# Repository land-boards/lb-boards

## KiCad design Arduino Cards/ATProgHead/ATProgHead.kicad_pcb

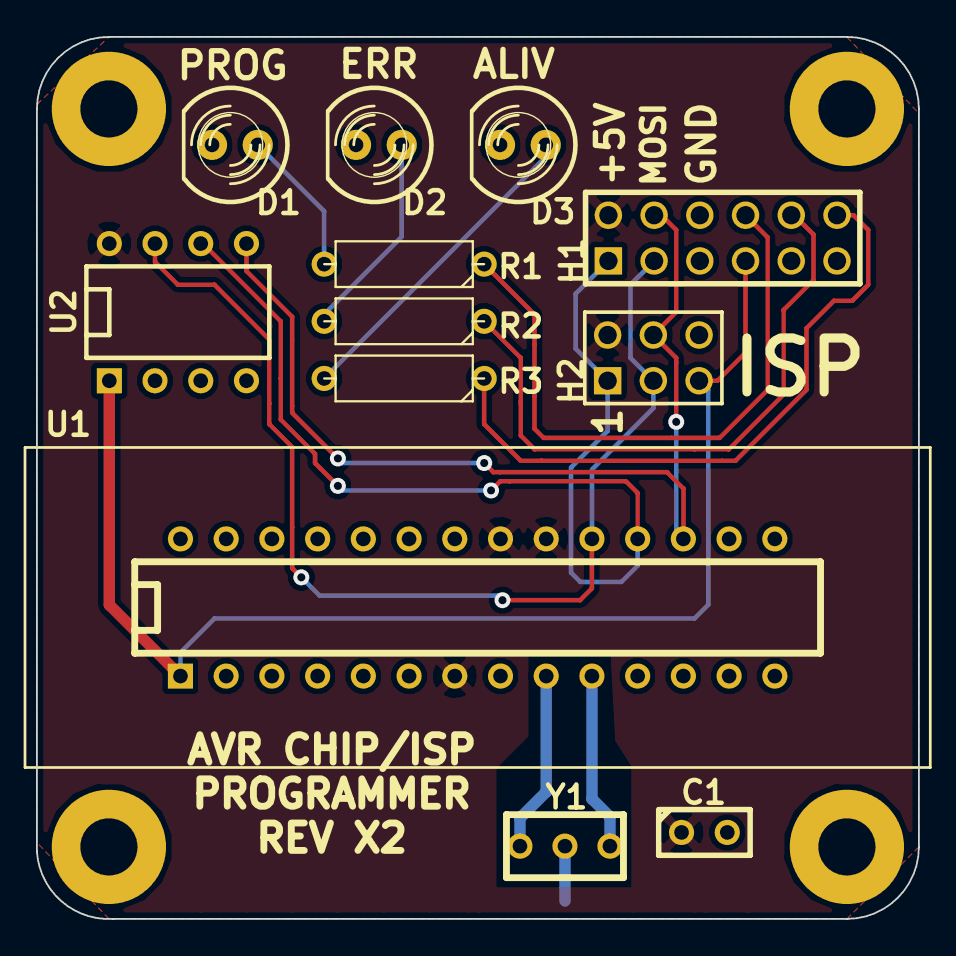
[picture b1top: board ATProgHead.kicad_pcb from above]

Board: 2 copper layers, 49.0 x 49.0 mm, 16 parts (0 on the bottom side), 14 nets.

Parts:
C1: 0.1uF; C1
D1, D2, D3: LED; LED-5MM
H1: CONN_6X2; pin_array_6x2
H2: CONN_3X2; pin_array_3x2
MTG1, MTG2, MTG3, MTG4: CONN_1; MTG-4-40
R1, R2, R3: 330; R3-5
U1: ATMEGA328-PU; TEXTOOL-28N
U2: ATTINY85; DIP-8__300
Y1: 16MHz; RESON_3PIN

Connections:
+5V: C1.1, H1.2, H2.2, U1.7, U1.20, U1.21, U2.8
/ER: D2.1, R2.2
/ERR-D8: H1.10, R2.1
/HB: D3.1, R3.2
/HTBT-D9: H1.12, R3.1
/MISO-D12: H1.1, H2.1, U1.18, U2.6
/MOSI-D11: H1.4, H2.4, U1.17, U2.5
/PG: D1.1, R1.2
/PROG-D7: H1.8, R1.1
/RST-D10: H1.7, H2.5, U1.1, U2.1
/SCK-D13: H1.3, H2.3, U1.19, U2.7
GND: C1.2, D1.2, D2.2, D3.2, H1.6, H2.6, U1.8, U1.22, U2.4, Y1.2
unnamed: U1.9, Y1.1
unnamed: U1.10, Y1.3

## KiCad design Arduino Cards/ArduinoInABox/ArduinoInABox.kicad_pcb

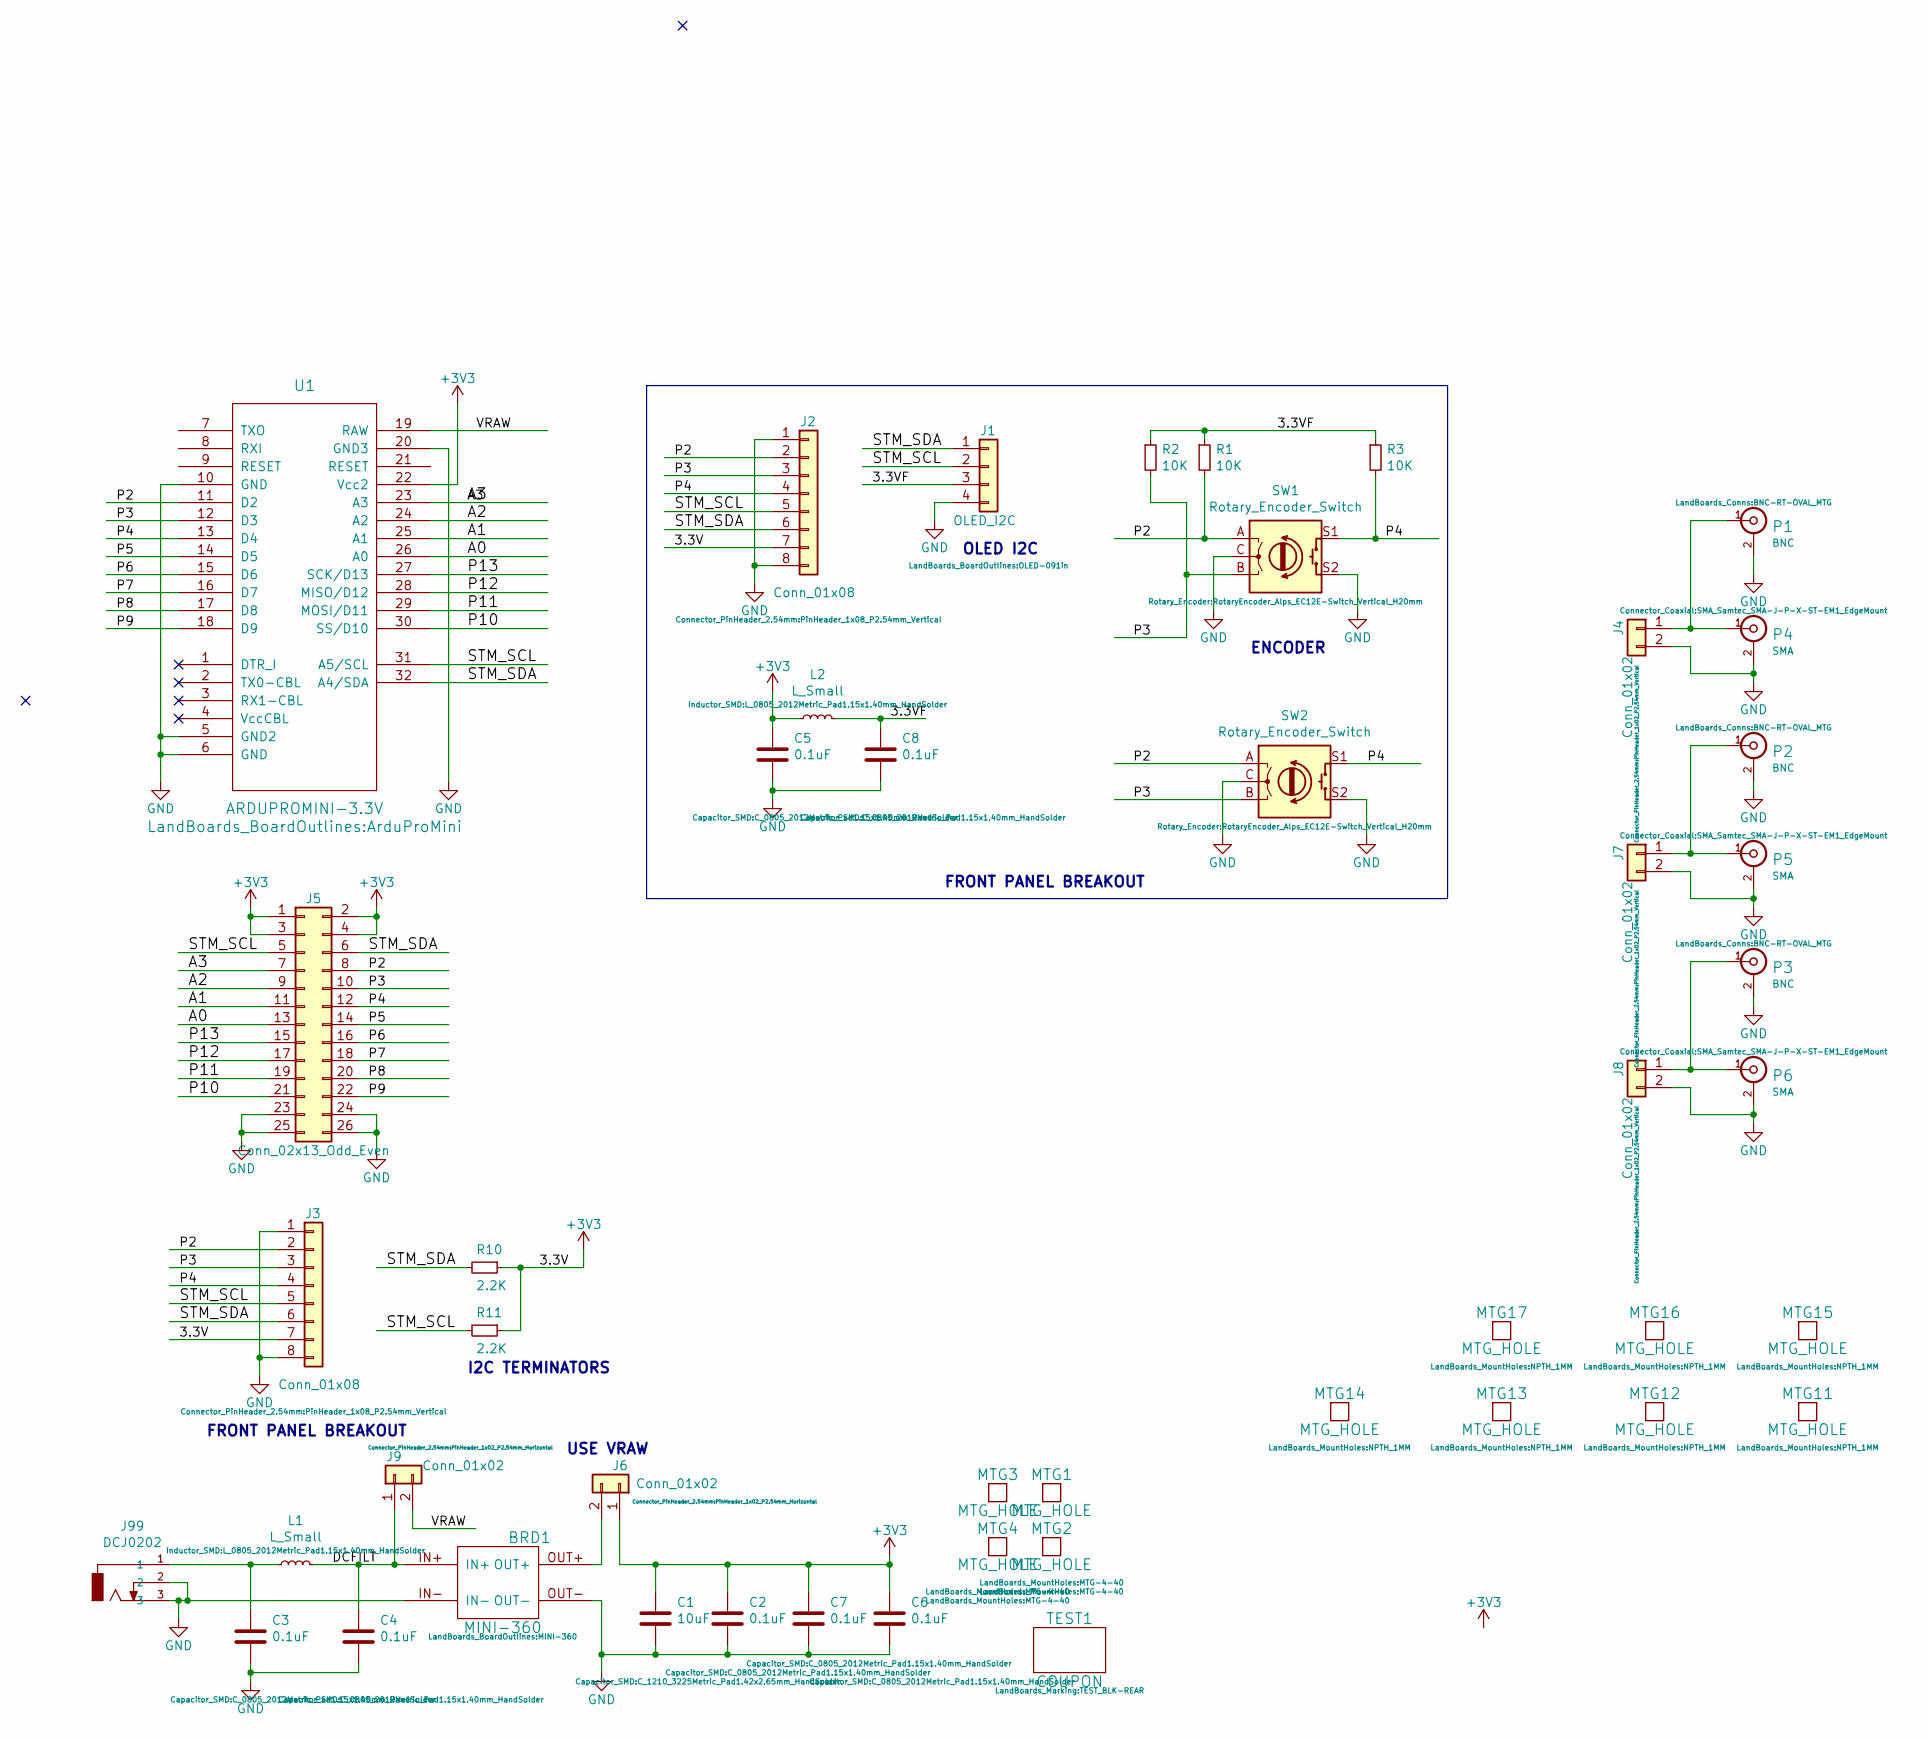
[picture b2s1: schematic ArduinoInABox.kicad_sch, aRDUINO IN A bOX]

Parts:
BRD1: MINI-360
C1: 10uF; C_1210_3225Metric_Pad1.42x2.65mm_HandSolder
C2, C3, C4, C5, C6, C7, C8: 0.1uF; C_0805_2012Metric_Pad1.15x1.40mm_HandSolder
J1: OLED_I2C; OLED-091in
J2, J3: Conn_01x08; PinHeader_1x08_P2.54mm_Vertical
J4, J7, J8: Conn_01x02; PinHeader_1x02_P2.54mm_Vertical
J5: Conn_02x13_Odd_Even; PinHeader_2x13_P2.54mm_Vertical
J6, J9: Conn_01x02; PinHeader_1x02_P2.54mm_Horizontal
J99: DCJ0202; DCJ-NEW-Slotted
L1, L2: L_Small; L_0805_2012Metric_Pad1.15x1.40mm_HandSolder
MTG1, MTG2, MTG3, MTG4: MTG_HOLE; MTG-4-40
MTG11, MTG12, MTG13, MTG14, MTG15, MTG16, MTG17: MTG_HOLE; NPTH_1MM
P1, P2, P3: BNC; BNC-RT-OVAL_MTG
P4, P5, P6: SMA; SMA_Samtec_SMA-J-P-X-ST-EM1_EdgeMount
R1, R2, R3: 10K; R_0805_2012Metric_Pad1.15x1.40mm_HandSolder
R10, R11: 2.2K; R_0805_2012Metric_Pad1.15x1.40mm_HandSolder
SW1, SW2: Rotary_Encoder_Switch; RotaryEncoder_Alps_EC12E-Switch_Vertical_H20mm
TEST1: COUPON; TEST_BLK-REAR
U1: ARDUPROMINI-3.3V; ArduProMini

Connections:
+3V3: C1.1, C2.1, C5.1, C6.1, C7.1, J2.7, J3.7, J5.1, J5.2, J5.3, J5.4, J6.1, L2.1, R10.1, R11.1, U1.22 (Vcc2)
/3.3VF: C8.1, J1.3, L2.2, R1.1, R2.1, R3.1
/A0: J5.13, U1.26 (A0)
/A1: J5.11, U1.25 (A1)
/A2: J5.9, U1.24 (A2)
/A3: J5.7, U1.23 (A3)
/DCFILT: BRD1.IN+, C4.1, J9.1, L1.2
/P2: J2.2, J3.2, J5.8, R1.2, SW1.A, SW2.A, U1.11 (D2)
/P3: J2.3, J3.3, J5.10, R2.2, SW1.B, SW2.B, U1.12 (D3)
/P4: J2.4, J3.4, J5.12, R3.2, SW1.S1, SW2.S1, U1.13 (D4)
/P5: J5.14, U1.14 (D5)
/P6: J5.16, U1.15 (D6)
/P7: J5.18, U1.16 (D7)
/P8: J5.20, U1.17 (D8)
/P9: J5.22, U1.18 (D9)
/P10: J5.21, U1.30 (SS/D10)
/P11: J5.19, U1.29 (MOSI/D11)
/P12: J5.17, U1.28 (MISO/D12)
/P13: J5.15, U1.27 (SCK/D13)
/STM_SCL: J1.2, J2.5, J3.5, J5.5, R11.2, U1.31 (A5/SCL)
/STM_SDA: J1.1, J2.6, J3.6, J5.6, R10.2, U1.32 (A4/SDA)
/VRAW: J9.2, U1.19 (RAW)
GND: BRD1.IN-, BRD1.OUT-, C1.2, C2.2, C3.2, C4.2, C5.2, C6.2, C7.2, C8.2, J1.4, J2.1, J2.8, J3.1, J3.8, J4.2, J5.23, J5.24, J5.25, J5.26, J7.2, J8.2, J99.2, J99.3, P1.2 (Ext), P2.2 (Ext), P3.2 (Ext), P4.2 (Ext), P5.2 (Ext), P6.2 (Ext), SW1.C, SW1.S2, SW2.C, SW2.S2, U1.5 (GND2), U1.6 (GND), U1.10 (GND), U1.20 (GND3)
unnamed: BRD1.OUT+, J6.2
unnamed: C3.1, J99.1, L1.1
unnamed: J4.1, P1.1 (In), P4.1 (In)
unnamed: J7.1, P2.1 (In), P5.1 (In)
unnamed: J8.1, P3.1 (In), P6.1 (In)

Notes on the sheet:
OLED I2C
FRONT PANEL BREAKOUT
USE VRAW
ENCODER
I2C TERMINATORS

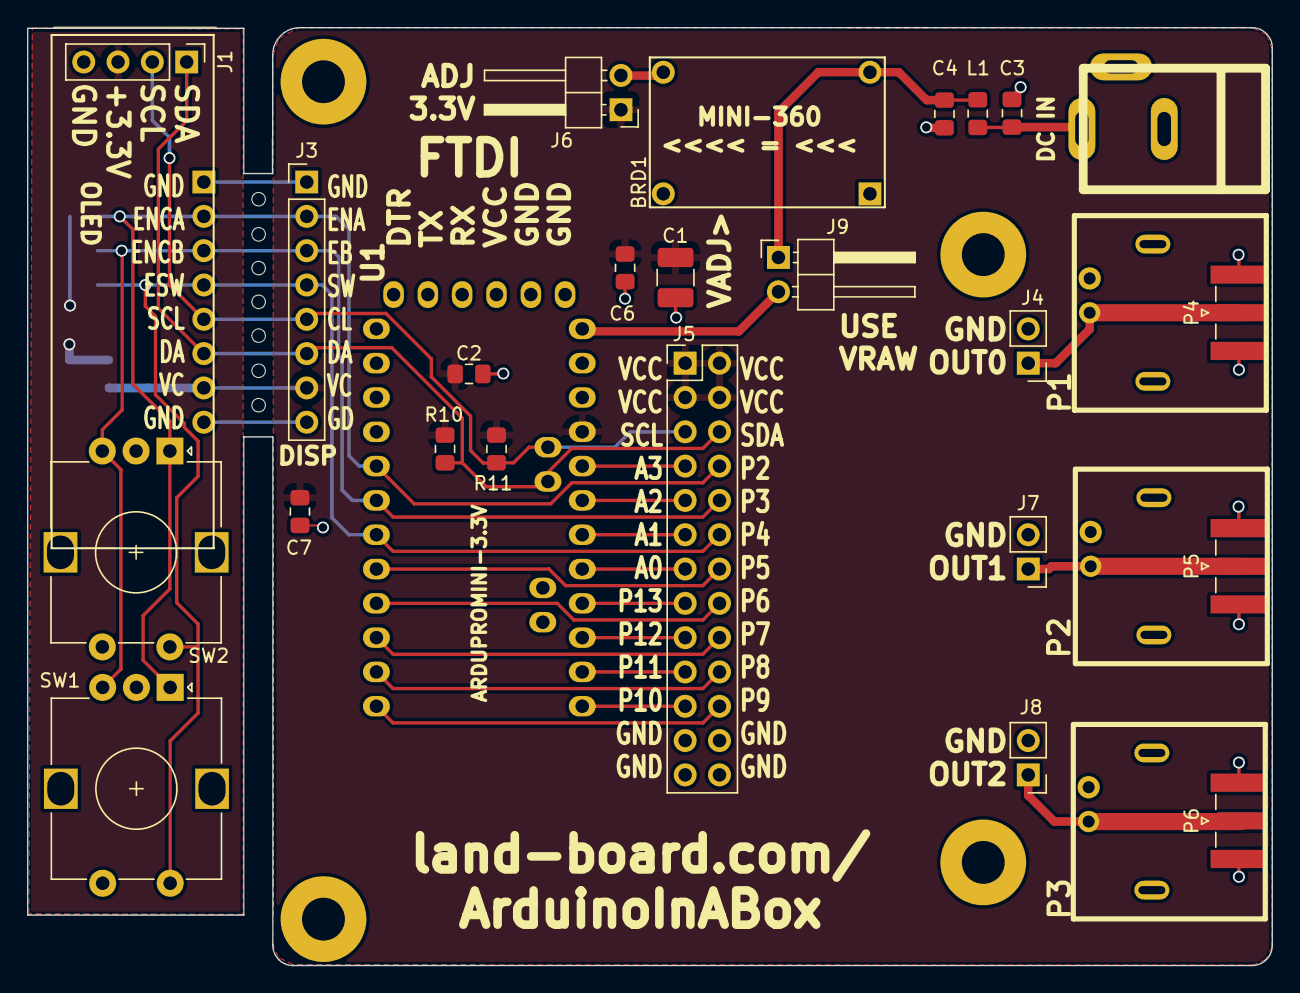
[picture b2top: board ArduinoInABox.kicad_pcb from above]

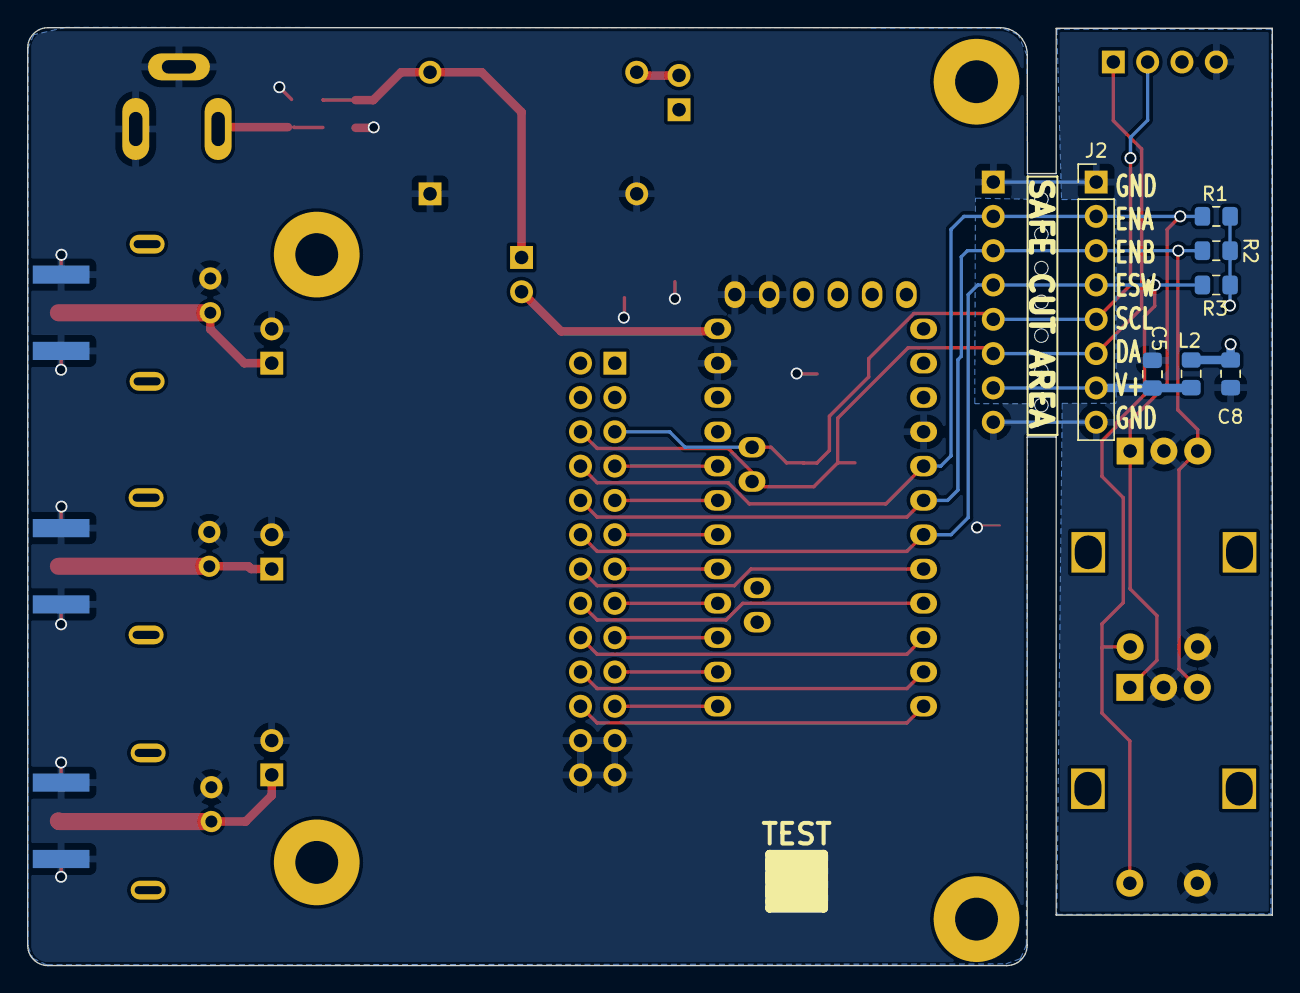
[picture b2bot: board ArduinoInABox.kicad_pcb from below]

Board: 2 copper layers, 92.2 x 69.4 mm, 47 parts (7 on the bottom side), 28 nets.

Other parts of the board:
TEST: COUPON; TEST_BLK-REAR

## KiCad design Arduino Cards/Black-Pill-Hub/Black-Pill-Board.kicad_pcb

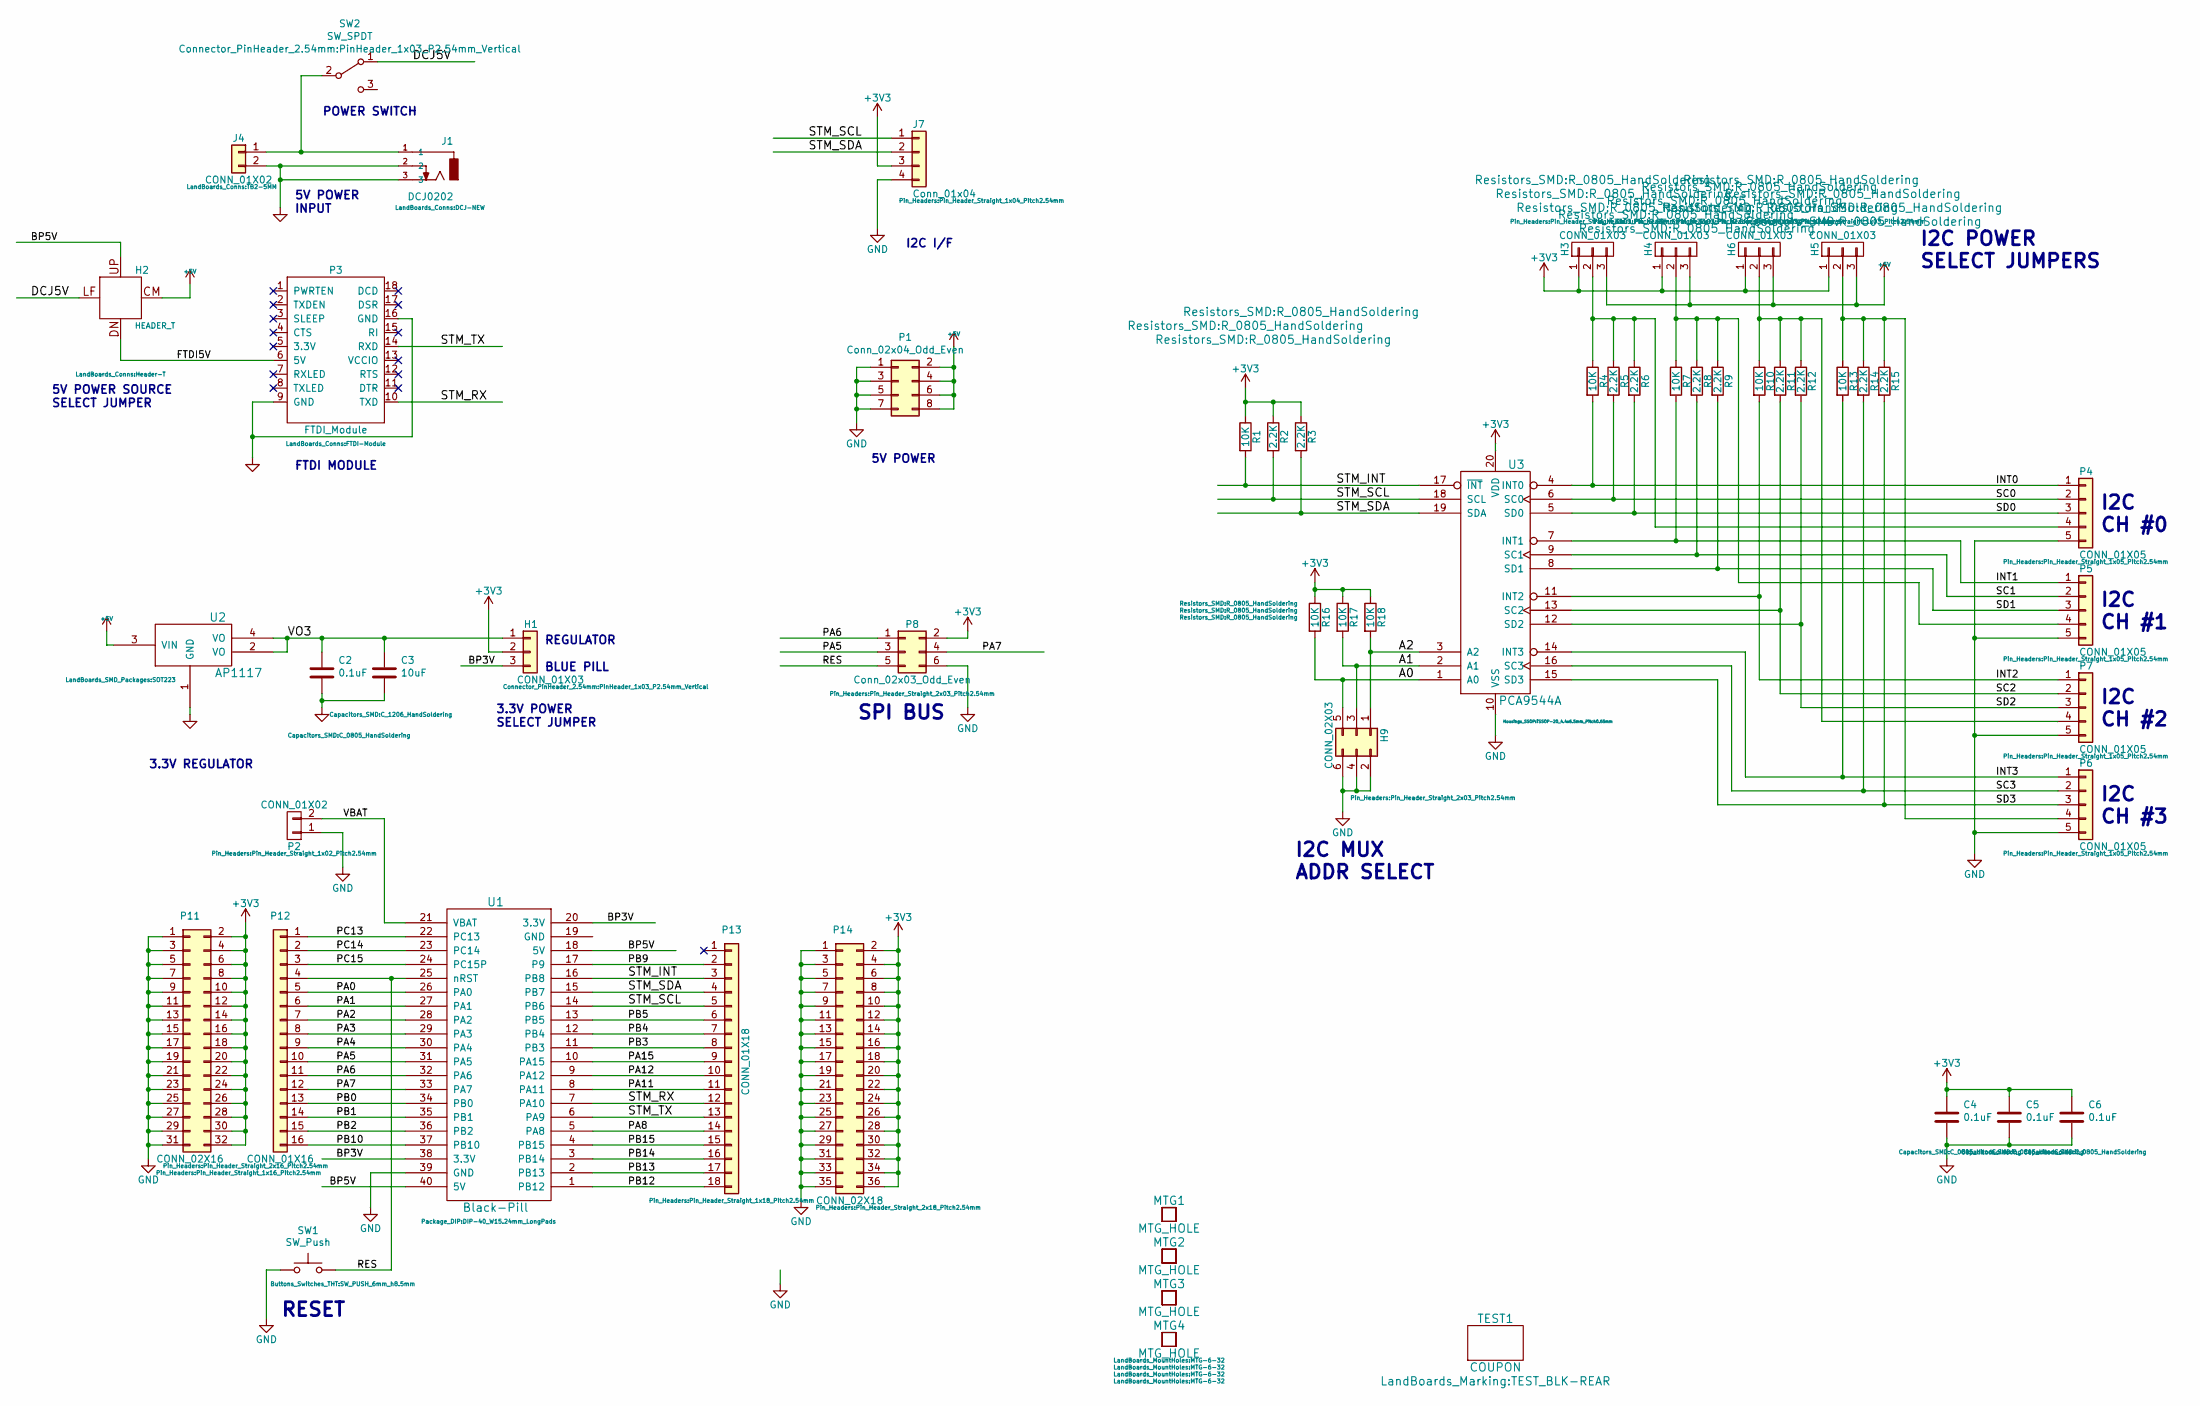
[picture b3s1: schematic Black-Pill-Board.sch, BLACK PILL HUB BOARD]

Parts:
C2, C4, C5, C6: 0.1uF; C_0805_HandSoldering
C3: 10uF; C_1206_HandSoldering
H1: CONN_01X03; PinHeader_1x03_P2.54mm_Vertical
H2: HEADER_T; Header-T
H3, H4, H5, H6: CONN_01X03; Pin_Header_Straight_1x03_Pitch2.54mm
H9: CONN_02X03; Pin_Header_Straight_2x03_Pitch2.54mm
J1: DCJ0202; DCJ-NEW
J4: CONN_01X02; TB2-5MM
J7: Conn_01x04; Pin_Header_Straight_1x04_Pitch2.54mm
MTG1, MTG2, MTG3, MTG4: MTG_HOLE; MTG-6-32
P1: Conn_02x04_Odd_Even; PinHeader_2x04_P2.54mm_Vertical
P2: CONN_01X02; Pin_Header_Straight_1x02_Pitch2.54mm
P3: FTDI_Module; FTDI-Module
P4, P5, P6, P7: CONN_01X05; Pin_Header_Straight_1x05_Pitch2.54mm
P8: Conn_02x03_Odd_Even; Pin_Header_Straight_2x03_Pitch2.54mm
P11: CONN_02X16; Pin_Header_Straight_2x16_Pitch2.54mm
P12: CONN_01X16; Pin_Header_Straight_1x16_Pitch2.54mm
P13: CONN_01X18; Pin_Header_Straight_1x18_Pitch2.54mm
P14: CONN_02X18; Pin_Header_Straight_2x18_Pitch2.54mm
R1, R4, R7, R10, R13, R16, R17, R18: 10K; R_0805_HandSoldering
R2, R3, R5, R6, R8, R9, R11, R12, R14, R15: 2.2K; R_0805_HandSoldering
SW1: SW_Push; SW_PUSH_6mm_h8.5mm
SW2: SW_SPDT; PinHeader_1x03_P2.54mm_Vertical
TEST1: COUPON; TEST_BLK-REAR
U1: Black-Pill; DIP-40_W15.24mm_LongPads
U2: AP1117; SOT223
U3: PCA9544A; TSSOP-20_4.4x6.5mm_Pitch0.65mm

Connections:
+3V3: C4.1, C5.1, C6.1, H1.2, H3.1, H4.1, H5.1, H6.1, J7.3, P8.2, P11.2, P11.4, P11.6, P11.8, P11.10, P11.12, P11.14, P11.16, P11.18, P11.20, P11.22, P11.24, P11.26, P11.28, P11.30, P11.32, P14.2, P14.4, P14.6, P14.8, P14.10, P14.12, P14.14, P14.16, P14.18, P14.20, P14.22, P14.24, P14.26, P14.28, P14.30, P14.32, P14.34, P14.36, R1.1, R2.1, R3.1, R16.1, R17.1, R18.1, U3.20 (VDD)
+5V: H2.CM (COM), H3.3, H4.3, H5.3, H6.3, P1.2, P1.4, P1.6, P1.8, U2.3 (VIN)
/A0: H9.5, R16.2, U3.1 (A0)
/A1: H9.3, R17.2, U3.2 (A1)
/A2: H9.1, R18.2, U3.3 (A2)
/BP3V: H1.3, U1.20 (3.3V), U1.38 (3.3V)
/BP5V: H2.UP, U1.18 (5V), U1.40 (5V)
/DCJ5V: H2.LF (LEFT), SW2.1 (A)
/FTDI5V: H2.DN (DOWN), P3.6 (5V)
/INT0: P4.1, R4.2, U3.4 (INT0)
/INT1: P5.1, R7.2, U3.7 (INT1)
/INT2: P7.1, R10.2, U3.11 (INT2)
/INT3: P6.1, R13.2, U3.14 (INT3)
/PA0: P12.5, U1.26 (PA0)
/PA1: P12.6, U1.27 (PA1)
/PA2: P12.7, U1.28 (PA2)
/PA3: P12.8, U1.29 (PA3)
/PA4: P12.9, U1.30 (PA4)
/PA5: P8.3, P12.10, U1.31 (PA5)
/PA6: P8.1, P12.11, U1.32 (PA6)
/PA7: P8.4, P12.12, U1.33 (PA7)
/PA8: P13.14, U1.5 (PA8)
/PA11: P13.11, U1.8 (PA11)
/PA12: P13.10, U1.9 (PA12)
/PA15: P13.9, U1.10 (PA15)
/PB0: P12.13, U1.34 (PB0)
/PB1: P12.14, U1.35 (PB1)
/PB2: P12.15, U1.36 (PB2)
/PB3: P13.8, U1.11 (PB3)
/PB4: P13.7, U1.12 (PB4)
/PB5: P13.6, U1.13 (PB5)
/PB9: P13.2, U1.17 (P9)
/PB10: P12.16, U1.37 (PB10)
/PB12: P13.18, U1.1 (PB12)
/PB13: P13.17, U1.2 (PB13)
/PB14: P13.16, U1.3 (PB14)
/PB15: P13.15, U1.4 (PB15)
/PC13: P12.1, U1.22 (PC13)
/PC14: P12.2, U1.23 (PC14)
/PC15: P12.3, U1.24 (PC15P)
/RES: P8.5, P12.4, SW1.2, U1.25 (nRST)
/SC0: P4.2, R5.2, U3.6 (SC0)
/SC1: P5.2, R8.2, U3.9 (SC1)
/SC2: P7.2, R11.2, U3.13 (SC2)
/SC3: P6.2, R14.2, U3.16 (SC3)
/SD0: P4.3, R6.2, U3.5 (SD0)
/SD1: P5.3, R9.2, U3.8 (SD1)
/SD2: P7.3, R12.2, U3.12 (SD2)
/SD3: P6.3, R15.2, U3.15 (SD3)
/STM_INT: P13.3, R1.2, U1.16 (PB8), U3.17 (~INT)
/STM_RX: P3.10 (TXD), P13.12, U1.7 (PA10)
/STM_SCL: J7.1, P13.5, R2.2, U1.14 (PB6), U3.18 (SCL)
/STM_SDA: J7.2, P13.4, R3.2, U1.15 (PB7), U3.19 (SDA)
/STM_TX: P3.14 (RXD), P13.13, U1.6 (PA9)
/VBAT: P2.2, U1.21 (VBAT)
/VO3: C2.1, C3.1, H1.1, U2.2 (VO), U2.4 (VO)
GND: C2.2, C3.2, C4.2, C5.2, C6.2, H9.2, H9.4, H9.6, J1.2, J1.3, J4.2, J7.4, P1.1, P1.3, P1.5, P1.7, P2.1, P3.9 (GND), P3.16 (GND), P4.5, P5.5, P6.5, P7.5, P8.6, P11.1, P11.3, P11.5, P11.7, P11.9, P11.11, P11.13, P11.15, P11.17, P11.19, P11.21, P11.23, P11.25, P11.27, P11.29, P11.31, P14.1, P14.3, P14.5, P14.7, P14.9, P14.11, P14.13, P14.15, P14.17, P14.19, P14.21, P14.23, P14.25, P14.27, P14.29, P14.31, P14.33, P14.35, SW1.1, U1.39 (GND), U2.1 (GND), U3.10 (VSS)
unnamed: H3.2, P4.4, R4.1, R5.1, R6.1
unnamed: H4.2, P5.4, R7.1, R8.1, R9.1
unnamed: H5.2, P6.4, R13.1, R14.1, R15.1
unnamed: H6.2, P7.4, R10.1, R11.1, R12.1
unnamed: J1.1, J4.1, SW2.2 (B)

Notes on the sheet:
FTDI MODULE
SPI BUS
RESET
I2C I/F
POWER SWITCH
5V POWER INPUT
5V POWER SOURCE SELECT JUMPER
I2C MUX ADDR SELECT
I2C CH #0
I2C CH #1
I2C CH #2
I2C CH #3
I2C POWER SELECT JUMPERS
3.3V REGULATOR
3.3V POWER SELECT JUMPER
REGULATOR BLUE PILL
5V POWER

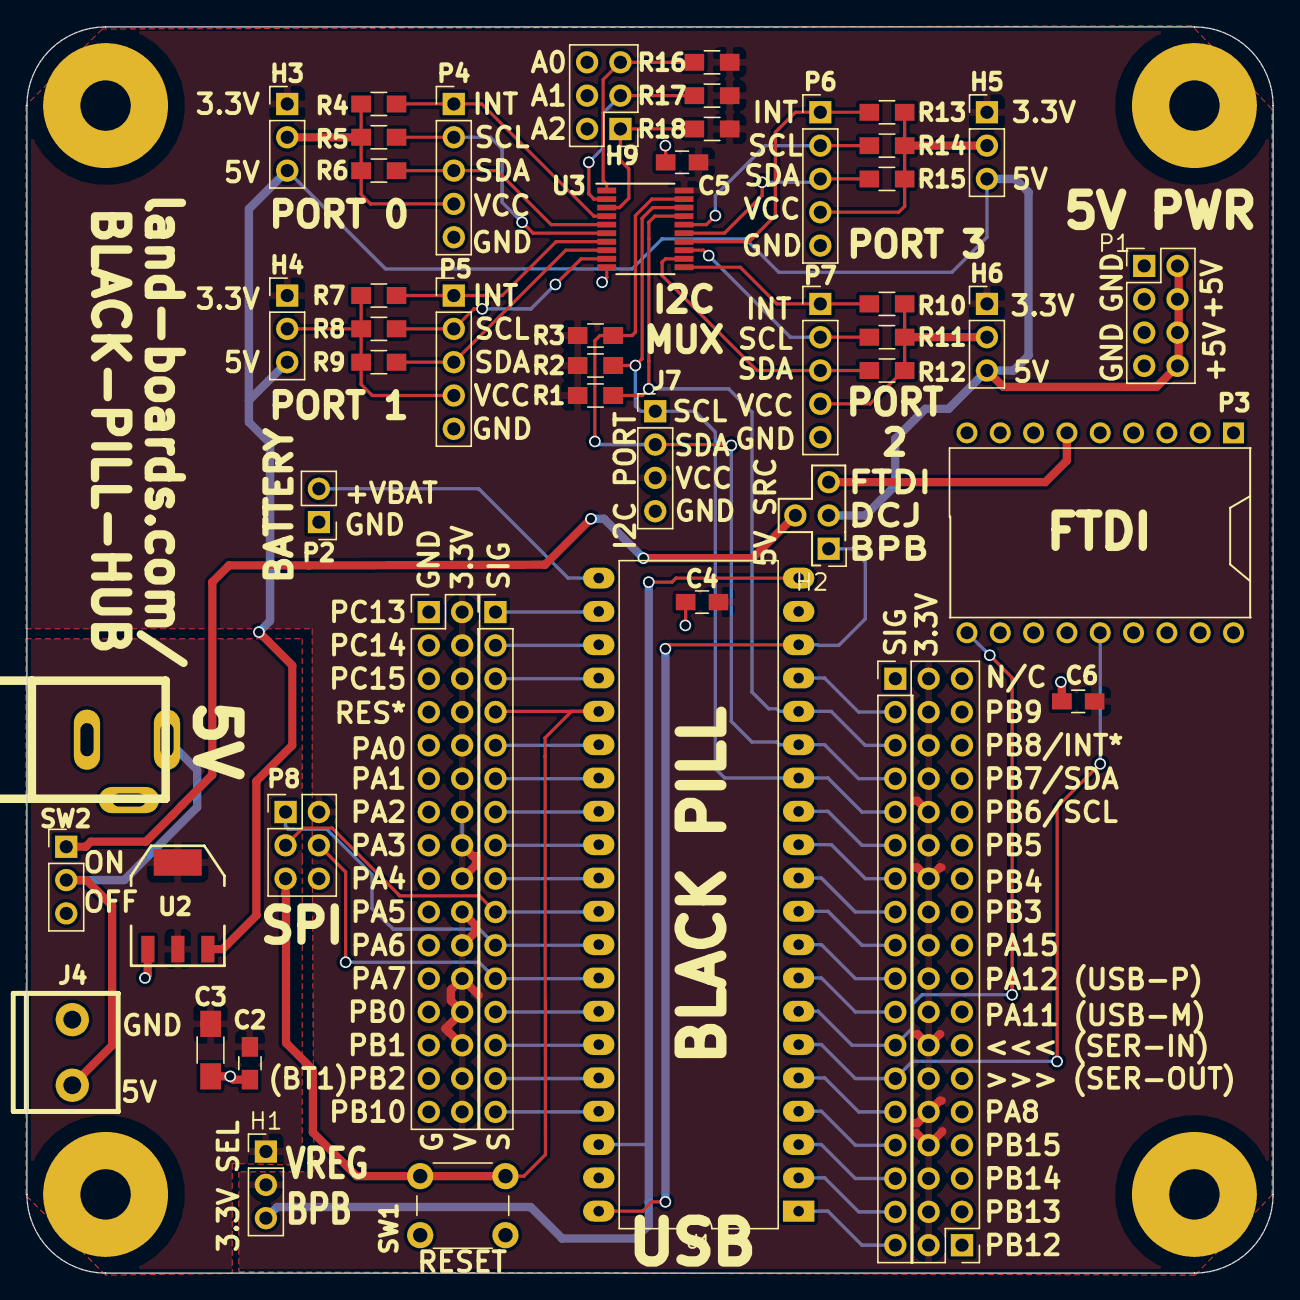
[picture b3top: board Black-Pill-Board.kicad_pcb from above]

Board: 2 copper layers, 95.0 x 95.0 mm, 55 parts (0 on the bottom side), 62 nets.

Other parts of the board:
TEST: COUPON; TEST_BLK-REAR

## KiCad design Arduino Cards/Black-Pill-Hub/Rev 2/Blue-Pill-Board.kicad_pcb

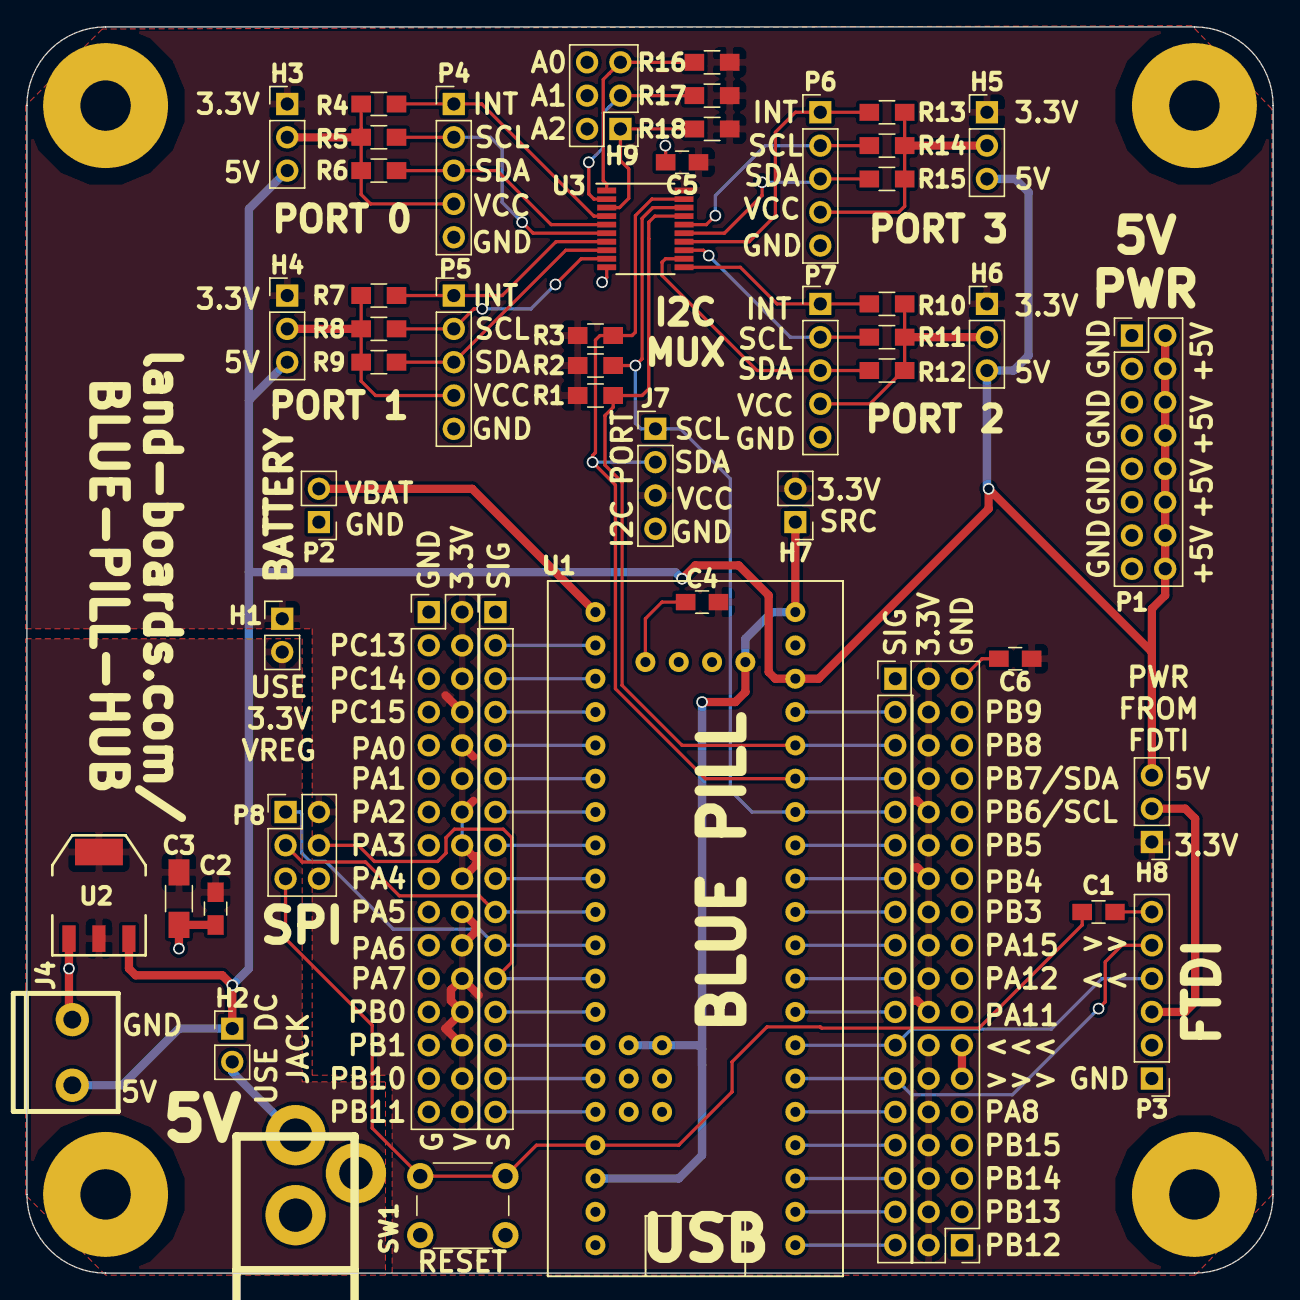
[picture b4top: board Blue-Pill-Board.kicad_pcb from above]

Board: 2 copper layers, 95.0 x 95.0 mm, 56 parts (0 on the bottom side), 61 nets.

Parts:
C1, C2, C4, C5, C6: 0.1uF; C_0805_HandSoldering
C3: 10uF; C_1206_HandSoldering
H1, H2, H7: CONN_01X02; Pin_Header_Straight_1x02_Pitch2.54mm
H3, H4, H5, H6, H8: CONN_01X03; Pin_Header_Straight_1x03_Pitch2.54mm
H9: CONN_02X03; Pin_Header_Straight_2x03_Pitch2.54mm
J1: DCJ0202; DCJ-NEW
J4: CONN_01X02; TB2-5MM
J7: Conn_01x04; Pin_Header_Straight_1x04_Pitch2.54mm
MTG1, MTG2, MTG3: MTG_HOLE; MTG-6-32
MTG?1: MTG_HOLE; MTG-6-32
P1: Conn_02x08_Odd_Even; Pin_Header_Straight_2x08_Pitch2.54mm
P2: CONN_01X02; Pin_Header_Straight_1x02_Pitch2.54mm
P3: FTDI; Pin_Header_Straight_1x06_Pitch2.54mm
P4, P5, P6, P7: CONN_01X05; Pin_Header_Straight_1x05_Pitch2.54mm
P8: Conn_02x03_Odd_Even; Pin_Header_Straight_2x03_Pitch2.54mm
P11: CONN_02X16; Pin_Header_Straight_2x16_Pitch2.54mm
P12: CONN_01X16; Pin_Header_Straight_1x16_Pitch2.54mm
P13: CONN_01X18; Pin_Header_Straight_1x18_Pitch2.54mm
P14: CONN_02X18; Pin_Header_Straight_2x18_Pitch2.54mm
R1, R4, R7, R10, R13, R16, R17, R18: 10K; R_0805_HandSoldering
R2, R3, R5, R6, R8, R9, R11, R12, R14, R15: 2.2K; R_0805_HandSoldering
SW1: SW_Push; SW_PUSH_6mm_h8.5mm
U1: BP; BLUEPILL
U2: AP1117; SOT223
U3: PCA9544A; TSSOP-20_4.4x6.5mm_Pitch0.65mm

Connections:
+3V3: C4.1, C5.1, C6.1, H1.1, H3.1, H4.1, H5.1, H6.1, H7.2, H8.1, J7.3, P8.2, P11.2, P11.4, P11.6, P11.8, P11.10, P11.12, P11.14, P11.16, P11.18, P11.20, P11.22, P11.24, P11.26, P11.28, P11.30, P11.32, P14.2, P14.4, P14.6, P14.8, P14.10, P14.12, P14.14, P14.16, P14.18, P14.20, P14.22, P14.24, P14.26, P14.28, P14.30, P14.32, P14.34, P14.36, R1.1, R2.1, R3.1, R16.1, R17.1, R18.1, U3.20
+5V: H2.1, H3.3, H4.3, H5.3, H6.3, H8.3, J4.1, P1.2, P1.4, P1.6, P1.8, P1.10, P1.12, P1.14, P1.16, U1.5V, U2.3
/A0: H9.5, R16.2, U3.1
/A1: H9.3, R17.2, U3.2
/A2: H9.1, R18.2, U3.3
/DCIN: H2.2, J1.1
/INT0: P4.1, R4.2, U3.4
/INT1: P5.1, R7.2, U3.7
/INT2: P7.1, R10.2, U3.11
/INT3: P6.1, R13.2, U3.14
/PA0: P12.5, U1.PA0
/PA1: P12.6, U1.PA1
/PA2: P12.7, U1.PA2
/PA3: P12.8, U1.PA3
/PA4: P12.9, U1.PA4
/PA5: P8.3, P12.10, U1.PA5
/PA6: P8.1, P12.11, U1.PA6
/PA7: P8.4, P12.12, U1.PA7
/PA8: P13.14, U1.PA8
/PA11: P13.11, U1.PA11
/PA12: P13.10, U1.PA12
/PA15: P13.9, U1.PA15
/PB0: P12.13, U1.PB0
/PB1: P12.14, U1.PB1
/PB3: P13.8, U1.PB3
/PB4: P13.7, U1.PB4
/PB5: P13.6, U1.PB5
/PB9: P13.2, U1.PB9
/PB10: P12.15, U1.PB10
/PB11: P12.16, U1.PB11
/PB12: P13.18, U1.PB12
/PB13: P13.17, U1.PB13
/PB14: P13.16, U1.PB14
/PB15: P13.15, U1.PB15
/PC13: P12.2, U1.PC13
/PC14: P12.3, U1.PC14
/PC15: P12.4, U1.PC15
/RES: C1.2, P8.5, SW1.2, U1.NRST
/SC0: P4.2, R5.2, U3.6
/SC1: P5.2, R8.2, U3.9
/SC2: P7.2, R11.2, U3.13
/SC3: P6.2, R14.2, U3.16
/SD0: P4.3, R6.2, U3.5
/SD1: P5.3, R9.2, U3.8
/SD2: P7.3, R12.2, U3.12
/SD3: P6.3, R15.2, U3.15
/STM_INT: P13.3, R1.2, U1.PB8, U3.17
/STM_RX: P3.4, P13.12, U1.PA10
/STM_SCL: J7.1, P13.5, R2.2, U1.PB6, U3.18
/STM_SDA: J7.2, P13.4, R3.2, U1.PB7, U3.19
/STM_TX: P3.5, P13.13, U1.PA9
/VBAT: P2.2, U1.VBAT
/VO3: C2.1, C3.1, H1.2, U2.2, U2.4
GND: C2.2, C3.2, C4.2, C5.2, C6.2, H9.2, H9.4, H9.6, J1.2, J1.3, J4.2, J7.4, P1.1, P1.3, P1.5, P1.7, P1.9, P1.11, P1.13, P1.15, P2.1, P3.1, P4.5, P5.5, P6.5, P7.5, P8.6, P11.1, P11.3, P11.5, P11.7, P11.9, P11.11, P11.13, P11.15, P11.17, P11.19, P11.21, P11.23, P11.25, P11.27, P11.29, P11.31, P14.1, P14.3, P14.5, P14.7, P14.9, P14.11, P14.13, P14.15, P14.17, P14.19, P14.21, P14.23, P14.25, P14.27, P14.29, P14.31, P14.33, P14.35, SW1.1, U1.G, U2.1, U3.10
unnamed: C1.1, P3.6
unnamed: H3.2, P4.4, R4.1, R5.1, R6.1
unnamed: H4.2, P5.4, R7.1, R8.1, R9.1
unnamed: H5.2, P6.4, R13.1, R14.1, R15.1
unnamed: H6.2, P7.4, R10.1, R11.1, R12.1
unnamed: H7.1, U1.3V3
unnamed: H8.2, P3.3

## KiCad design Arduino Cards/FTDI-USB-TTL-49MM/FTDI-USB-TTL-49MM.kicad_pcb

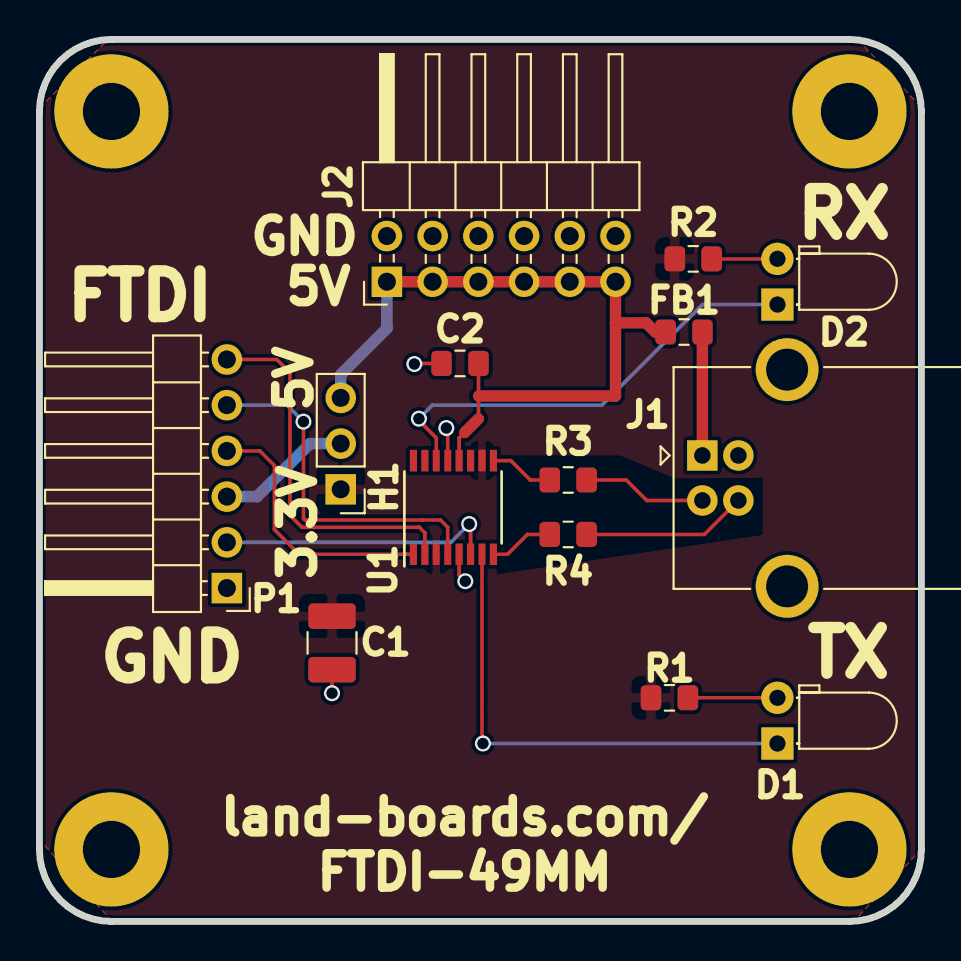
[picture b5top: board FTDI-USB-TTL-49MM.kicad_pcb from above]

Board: 2 copper layers, 49.0 x 49.0 mm, 16 parts (0 on the bottom side), 17 nets.

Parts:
BD-49X49: PCB_49MM; BD-49X49
C1: 10uF; C_1210_3225Metric_Pad1.42x2.65mm_HandSolder
C2: 0.1uF; C_0805_2012Metric_Pad1.15x1.40mm_HandSolder
D1, D2: LED_ALT; LED_D3.0mm_Horizontal_O1.27mm_Z2.0mm
FB1: Ferrite_Bead; R_0805_2012Metric_Pad1.15x1.40mm_HandSolder
H1: HDR, STRT, 13; PinHeader_1x03_P2.54mm_Vertical
J1: USB-B; USB_B_OST_USB-B1HSxx_Horizontal
J2: Conn_02x06_Odd_Even; PinHeader_2x06_P2.54mm_Horizontal
P1: HDR, RT ANG, 1x6; PinHeader_1x06_P2.54mm_Horizontal
R1, R2: 560; R_0805_2012Metric_Pad1.15x1.40mm_HandSolder
R3, R4: 22; R_0805_2012Metric_Pad1.15x1.40mm_HandSolder
TESTED: COUPON; TEST_BLK-REAR
U1: FT230XS; SSOP-16_3.9x4.9mm_P0.635mm

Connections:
/5VOUT: H1.2, P1.3
/+3.3V: C1.1, H1.1, R1.1, R2.1, U1.3, U1.10
/+5V: C2.1, FB1.1, H1.3, J2.1, J2.3, J2.5, J2.7, J2.9, J2.11, U1.12
/CTS: P1.2, U1.6
/DM: R3.2, U1.9
/DP: R4.2, U1.8
/PUP0: D1.2, R1.2
/PUP1: D2.2, R2.2
/RTS: P1.6, U1.2
/RX: P1.5, U1.4
/RXLED*: D2.1, U1.14
/TX: P1.4, U1.1
/TXLED*: D1.1, U1.7
GND: C1.2, C2.2, J1.4, J2.2, J2.4, J2.6, J2.8, J2.10, J2.12, P1.1, U1.5, U1.13
unnamed: FB1.2, J1.1
unnamed: J1.2, R3.1
unnamed: J1.3, R4.1
